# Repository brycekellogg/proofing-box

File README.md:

## TEC Element
Peltier element
CPU cooler 
fans

## TEC Controller

[Schematic]() | [BOM]() | [Layout]() | [Code]()

The "TEC Controller" is a sub-assmebly responsible for performing low level control operations
of the "TEC Element" in response to commands from the "Master Controller". Specifically, it
manages the following:
   - selecting a voltage level for the TEC
   - enabling/disabling the TEC
   - controlling FAN speed via a PWM signal
   - controlling TEC activation timing
   - controlling fan activation timing relative to TEC activation

The following diagram shows a high level view of the "TEC Controller":

![TEC block diagram][TEC Block Diagram]

#### Wiring Harnesses

   - [Power](https://google.com)
   - [Control]()
   - [Prog]()
   - [Element]()

#### Commands

 | Name            | Command Format | Response Format | Code Link |
 | --------------- | -------------- | --------------- | --------- |
 | Set Power Level | ???            |                 |           |

#### Programming

#### References
Fan pinout
datasheets

#### Notes
MOSFET Array: (used to select which power to connect to TEC+/-
    - https://www.digikey.com/en/products/detail/sanken/SLA5085/4289314

Interface
---------
   1. Power switch
   2. 2x knobs with detent & push switch
   3. LCD display

Electronics
-----------
Display: https://www.sparkfun.com/products/16397
Knob: https://www.digikey.com/en/products/detail/kilo-international/OEDNI-63-2-7/5970329

**Rotary Encoder:**
We want a rotary encoder with detent & a momentary push switch. Probably want something with threads so that
it can be screwed onto the cover panel.

Options on Sparkfun:
   - https://www.sparkfun.com/products/9117
   - https://www.sparkfun.com/products/16879

**Power switch:**
Toddle switch. SPDT ON-ON or ON-OFF-ON or ON-NONE-ON

Options on Digikey:
   - https://www.digikey.com/en/products/detail/e-switch/100SP1T1B1M1QEH/378819

Options on Sparkfun:
   - https://www.sparkfun.com/products/9276

Humidity Element
-----------------

Box
----
Plastic: 1/8" or 1/4" Komatex PVC
   - 12.5" x 12.5" (2x)
   - 12" x 16" (3x)
   - clear door (polycarbonate)
   - https://www.tapplastics.com/
   - PVC Cement 
Door: 1/8" or 1/4" clear polycarbonate
   - 12" x 16"
   - https://www.tapplastics.com/
   - Fridge rubber seal
   - hinges
   - latch
Insulation
Wood
Cable Gland
Rack

Internal Dimensions
--------------------
12" x 12" x 16"

[TEC Block Diagram]: ./images/tec-controller-block-diagram.png

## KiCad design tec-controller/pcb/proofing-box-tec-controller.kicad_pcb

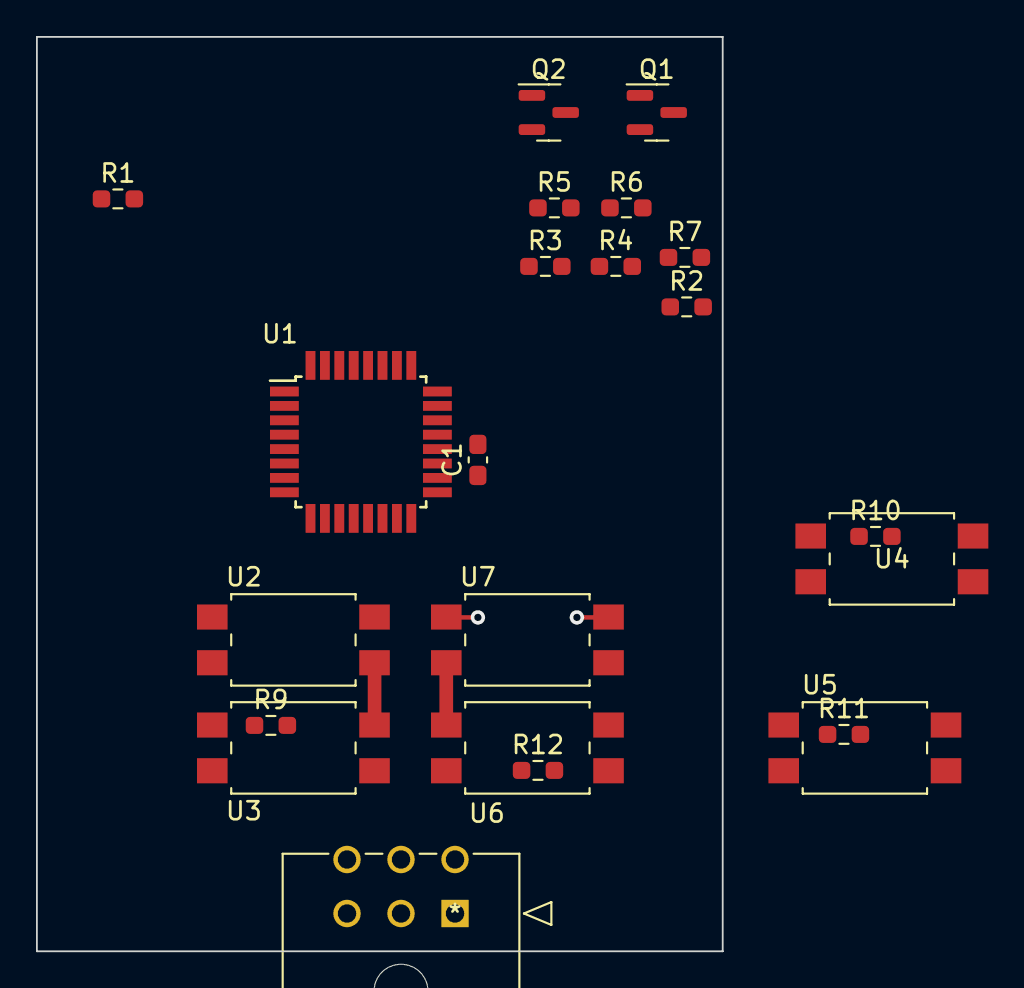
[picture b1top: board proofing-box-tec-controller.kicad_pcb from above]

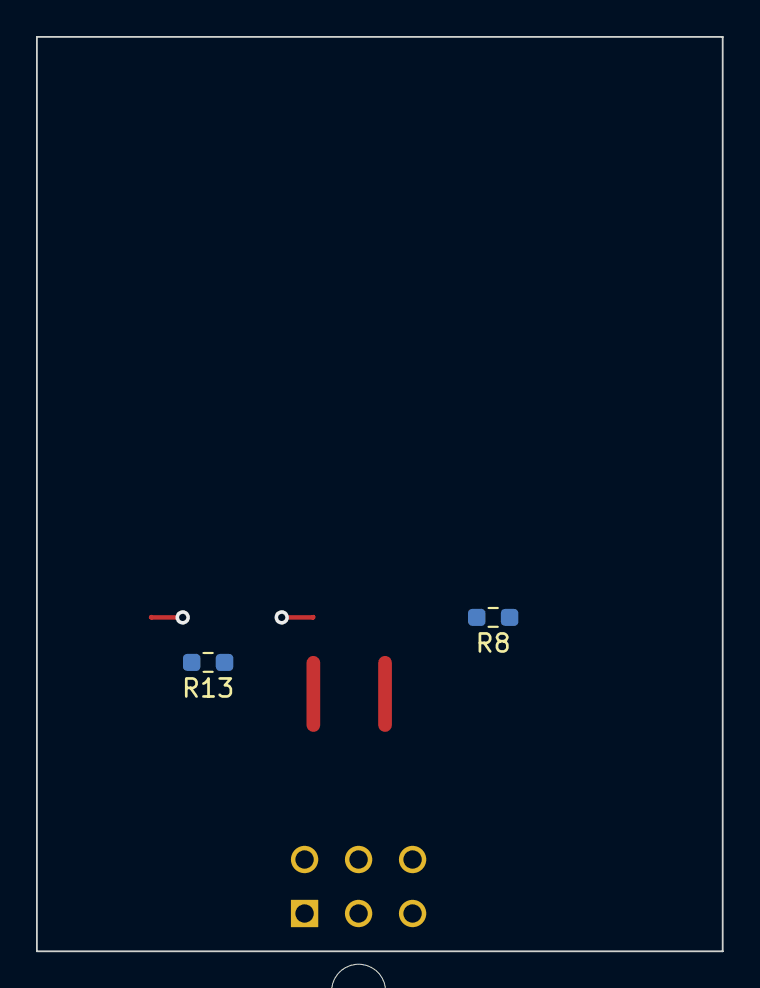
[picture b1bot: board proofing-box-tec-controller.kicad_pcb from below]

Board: 4 copper layers, 38.1 x 50.8 mm, 24 parts (2 on the bottom side), 24 nets.

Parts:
C1: C_Small; C_0603_1608Metric_Pad1.08x0.95mm_HandSolder
J4: Micro-Fit 2x3
Q1, Q2: BSS138; SOT-23
R1, R2, R3, R4, R5, R6, R7, R8, R9, R10, R11, R12, R13: R_US; R_0603_1608Metric_Pad0.98x0.95mm_HandSolder
U1: ATmega8L-8A; TQFP-32_7x7mm_P0.8mm
U2, U3, U4, U5, U6, U7: TLP241A

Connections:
+3.3V: Q1.1 (G), Q2.1 (G), R6.1, R7.1
+5V: C1.1, R1.1, R2.1, R3.1, R4.1, R5.1, U1.4 (VCC), U1.6 (VCC), U1.18 (AVCC), U2.4, U4.4, U5.4, U6.4
/FAN 0 CTRL: R10.2, U1.14 (PB2)
/FAN 0 PWR: J4.2, U4.3
/FAN 1 CTRL: R11.2, U1.13 (PB1)
/FAN 1 PWR: J4.3, U5.3
/PROG RST: R1.2, U1.29 (PC6/~RESET)
/SCL: Q1.3 (D), R3.2, R4.2, U1.28 (PC5)
/SDA: Q2.3 (D), R2.2, R5.2, U1.27 (PC4)
/TEC SW 0: R8.2, U1.30 (PD0)
/TEC SW 1: R9.2, U1.31 (PD1)
/TEC SW 2: R12.1, U1.32 (PD2)
/TEC SW 3: R13.1, U1.1 (PD3)
/TEC+: J4.4, U2.3, U3.4
/TEC-: J4.5, U6.3, U7.4
GND: C1.2, J4.6, U1.3 (GND), U1.5 (GND), U1.21 (AGND), U2.2, U3.2, U3.3, U4.2, U5.2, U6.2, U7.2, U7.3
unnamed: Q2.2 (S), R7.2
unnamed: Q1.2 (S), R6.2
unnamed: R8.1, U2.1
unnamed: R9.1, U3.1
unnamed: R10.1, U4.1
unnamed: R11.1, U5.1
unnamed: R12.2, U6.1
unnamed: R13.2, U7.1

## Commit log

2022-10-31 Initial commit of README & images
2022-11-01 Added sparkfun kicad libraries as a submodule
2022-11-19 [TEC Controller] added initial schematic symbols & footprint library
2022-11-19 Removed Sparkfun KiCAD libraries
2022-11-19 [TEC Controller] initial test schematic complete

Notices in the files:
parts and their libraries:
Copyright 2021 Accelerated Designs. All rights reserved.
